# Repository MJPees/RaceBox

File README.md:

# RaceCollection Überblick

Die **RaceCollection** ist ein System für den Miniatur-Automobilsport, das verschiedene Komponenten zur präzisen Zeiterfassung und Rennsteuerung bietet.

---

### RFID-Connector

Der **RFID-Connector** fungiert als RFID-Empfänger. Er erfasst Fahrzeuge präzise und übermittelt die Zieldurchfahrten an Rennmanagement-Software wie **SmartRace** oder **CH-Racing-Club**.<br><br>
<a href="./RFID-Connector/README.md">Zum RFID-Connector</a><br><br>

-----

### GhostCar / Startampel-LED mit GhostCar

Diese Komponente bietet eine **GhostCar-Funktion**, bei der Sie gegen einen Carrera Hybrid Racer antreten können. Sie beinhaltet auch eine **Startampel-LED**. Ein zugehöriges Video zeigt das "GhostCar-StartingLights"-System in Aktion mit der "SmartRace"-Software. Es demonstriert den Countdown der Startampel, das "Go"-Signal mit grünen Lichtern, die GhostCar-Funktionalität, die Rundenzeiterfassung und die Rennsteuerung.<br><br>
<a href="./GhostCar/README.md">Zum GhostCar</a><br>
<br><br>

-----

### Startampel Display

Das **Startampel Display** ist eine separate Anzeigeeinheit für die Startampel.<br><br>
<a href="./StartingLightsDisplay/README.md">Zur Startampel</a><br>
<br><br><br>

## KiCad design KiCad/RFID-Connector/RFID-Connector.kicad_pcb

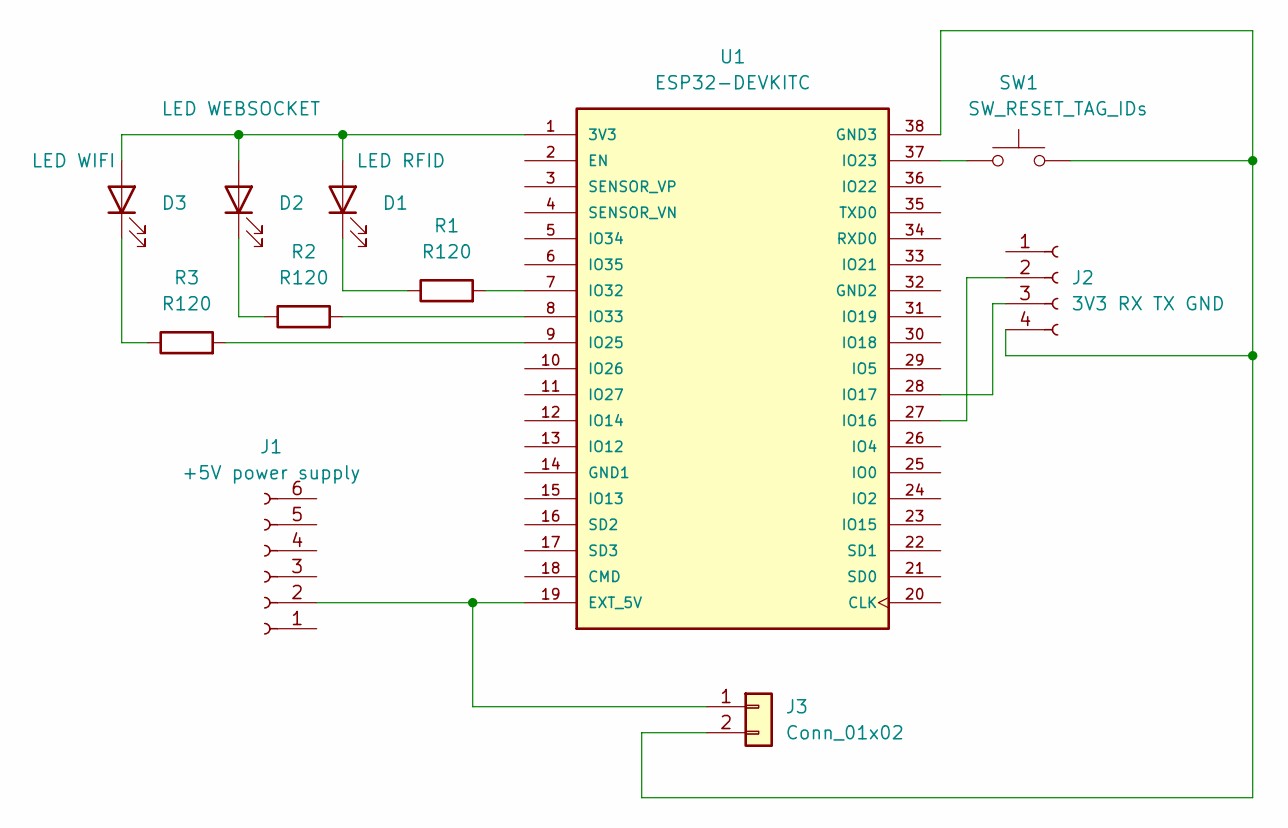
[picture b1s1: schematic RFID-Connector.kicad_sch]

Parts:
D1: LED RFID; LED_D3.0mm
D2: LED WEBSOCKET; LED_D3.0mm
D3: LED WIFI; LED_D3.0mm
J1: +5V power supply; PinHeader_1x06_P2.54mm_Vertical
J2: 3V3 RX TX GND; PinHeader_1x04_P2.54mm_Vertical
J3: Conn_01x02
R1, R2, R3: R120; R_Axial_DIN0204_L3.6mm_D1.6mm_P7.62mm_Horizontal
SW1: SW_RESET_TAG_IDs; SW_PUSH_6mm
U1: ESP32-DEVKITC; MODULE_ESP32-DEVKITC; PARTREV N/A

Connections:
unnamed: D1.1 (K), R1.1
unnamed: D1.2 (A), D2.2 (A), D3.2 (A), U1.1 (3V3)
unnamed: D2.1 (K), R2.1
unnamed: D3.1 (K), R3.1
unnamed: J1.2, J3.1, U1.19 (EXT_5V)
unnamed: J2.2, U1.27 (IO16)
unnamed: J2.3, U1.28 (IO17)
unnamed: J2.4, J3.2, SW1.2, U1.38 (GND3)
unnamed: R1.2, U1.7 (IO32)
unnamed: R2.2, U1.8 (IO33)
unnamed: R3.2, U1.9 (IO25)
unnamed: SW1.1, U1.37 (IO23)

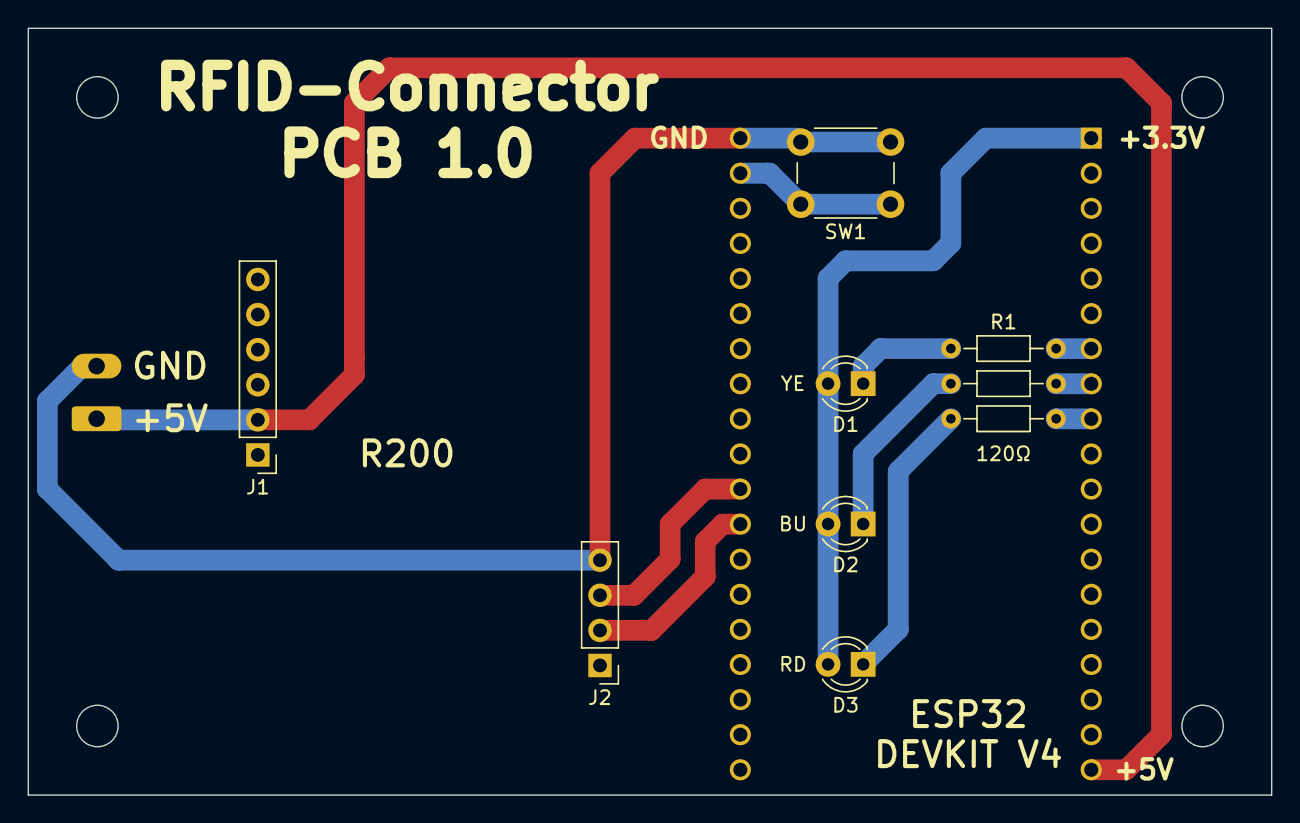
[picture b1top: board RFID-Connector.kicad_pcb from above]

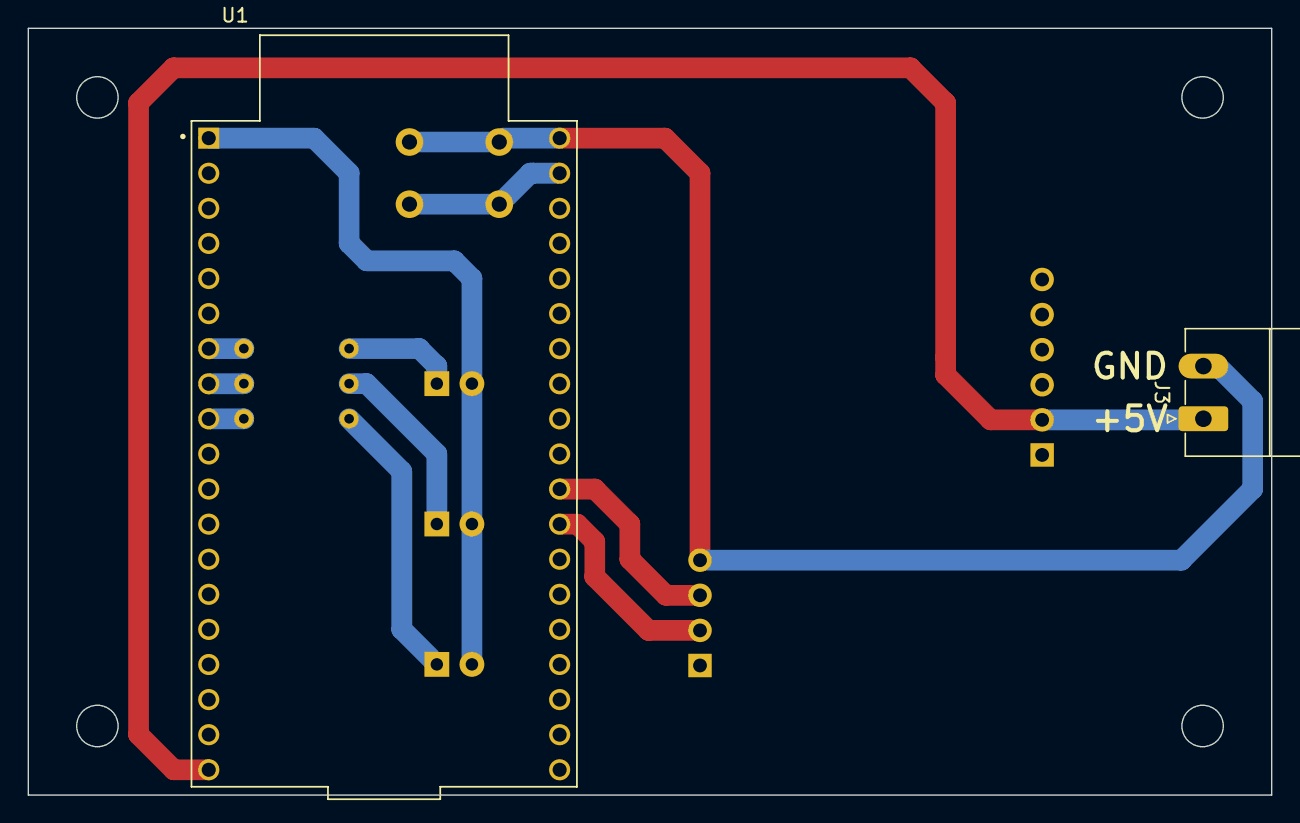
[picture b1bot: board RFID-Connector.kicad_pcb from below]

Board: 2 copper layers, 90.0 x 55.5 mm, 11 parts (2 on the bottom side), 12 nets.

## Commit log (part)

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2025-04-19 renamed ino file
2025-04-27 added Test
2025-04-27 deleted old files
2025-04-27 changes rfid read
2025-04-28 added wait time for startup rfid
2025-04-30 change power level from website
2025-04-30 removed r200 library
2025-05-01 fixed 11dbm value
2025-05-02 added images
2025-05-02 Erstentwurf Readme
2025-05-04 added min lap time to configuration (webpage)
2025-05-04 optimized min lap time
2025-05-04 fix optimized min lap time
2025-05-05 fixed 30 minutes timeout
2025-05-06 set power level without restart
2025-05-09 optimized communication
2025-05-09 changed bytes to unsigned char
2025-05-09 minor changes
2025-05-09 minor change
2025-05-09 8 cars possibel now. updated Readme
2025-05-09 updated images
2025-05-10 added Version information, Support for ESP32C3, added LapLed
2025-05-10 changed rx and tx pin at ESP32-C3 (wifi problems)
2025-05-10 bugfix wifi config
2025-05-10 bugfix dnsServer
2025-05-11 added setting led notification, fixed ap mode
2025-05-11 optimized startup
2025-05-11 added startup leds
2025-05-11 LAP LED bei ESP32-DEV auf D2 umgelegt, update Readme
2025-05-11 optimized r200 communication and wifi, bugfixes, LAP LED, ...
    - support for up to 8 cars
    - optimized r200 communication
    - fixed some wlan issues
    - added additional support for ESP32-C3
    - added optional LAP LED
2025-05-17 renamed led functions, added RFID label writer, updated Readme
2025-05-18 set wifi hostname to RFID-SmartRace
2025-05-20 hostname at webinterface, optimized performance of webinterface
2025-05-20 added CH-GhostCar-SmartRace
2025-05-20 CH-GhostCar-Smartrace - changed led pin
2025-05-21 feat: refactor default values, add CA to websocket client
2025-05-21 feat: optimize websocket reconnect
2025-05-21 feat: reduce magic numbers
2025-05-21 feat: make SSL CA certificate configurable via web interface
    - Added textarea field for ssl_ca_cert (PEM) in the configuration web page
    - ssl_ca_cert is now saved and loaded from preferences
    - Certificate is applied dynamically for websocket connections
    - Handles line breaks for compatibility with PEM format
2025-05-22 feat: replace unnecessary serverPort with apiKey in preferences
2025-05-22 feat(webui): add Alpine.js reactive select for targetSystem and conditional apiKey field
    - Integrated Alpine.js for reactive UI in the configuration web interface
    - Added select field for targetSystem with options "SmartRace" and "CH Racing Club"
    - ApiKey input is now only shown when "CH Racing Club" is selected
    - Preferences and config handling extended for targetSystem
2025-05-22 feat: adapt websocket payload format depending on selected target system
    - send_finish_line_message now builds the JSON payload differently for "ch_racing_club" and "smart_race"
    - For "ch_racing_club", sends command-based payload with api_key and rfid
    - For "smart_race", sends type-based payload with controller_id
    - Improves compatibility with multiple backend systems
2025-05-23 refactor: replace magic numbers for RFID counts with named constants
    - Introduced `RFID_MAX_COUNT` and `RFID_STORAGE_COUNT` to replace `max_rfid_cnt` and `storage_rfid_cnt`
    - Improved code clarity and maintainability by using named constants consistently
2025-05-23 refactor: extract WiFi reconnection logic into reloadWifi() helper
    - Moved repeated WiFi reconnection logic from `handleConfig()` to new `reloadWifi()` function
    - Improves code readability and reuse
2025-05-23 reduced magic numbers
2025-05-24 refactor: unify and extend configuration system with named fields
    - Replaced generic config variables with structured `config_*` names
    - Introduced `configuration_load()` and `configuration_save()` to encapsulate preferences handling
    - Added support for multiple target systems (`smart_race`, `ch_racing_club`)
    - Websocket and WiFi configuration now target-specific and modular
    - Renamed `reloadWifi()` to `wifi_reload()` for consistency
    - Improved serial output readability (prefixed log messages)
2025-05-24 refactor(checkRfid): simplify condition and avoid duplicate code
2025-05-25 feat: add JSON message formatting and deserialization with ArduinoJson
    - Use ArduinoJson to build and send websocket messages instead of manual string concatenation
    - Introduced lap time calculation for "ch_racing_club" payloads
    - Added JSON deserialization and error handling in `onMessageCallback()`
    - Improved log clarity with prefixed serial output
2025-05-25 fix: log prefix in onEventsCallback
2025-05-25 fix: websocket logging prefix
2025-05-25 chore: bump firmware version to 1.2.0
2025-05-25 fixed wifi reconnect , added simulator
2025-05-26 fixed webpage redirection
2025-05-26 fixed webpage redirect
2025-05-26 added websocket connected led
2025-05-27 disabled raising websocket backof for SmartRace, fixed websocket reconnect on wifi changes, optimized led functions
2025-05-31 fix: type of api key form input field
2025-05-31 feat: send target-specific connect message after websocket connection
    - Replaced hardcoded initial WebSocket messages with JSON payloads
    - Payload format now depends on `config_target_system`
    - `smart_race`: sends controller_set with controller_id "Z"
    - `ch_racing_club`: sends connect command with API key and device IP
2025-06-01 changed start multiRead
2025-06-01 fixed crash on wifi changes
2025-06-01 feat: send target-specific connect message after websocket connection (changed by endorfin)
2025-06-01 fix: possible crash on wifi changes, driving on config changes
2025-06-02 added hostname to serial output (only ble-mode)
2025-06-02 added hostname to serial output
2025-06-04 changed serial output, stop multiread at setReaderSetting()
2025-06-04 fixed stop multiRead on reboot of esp32
2025-06-04 ghostcar [ESP32-S3]: return to white led after braking (websocket connected led)
2025-06-04 fix: set lastEpcRead
2025-06-06 feat: dense-mode could be disabled for better rfid range
2025-06-07 ble + usb (2 Ghostcars) for ESP32S3
2025-06-07 renamed CH-GhostCar-SmartRace to RaceBox-GhostCar
2025-06-07 changed folder and ino-name of GhostCar
2025-06-07 renamed RFID-SmartRace to RaceBox. Added WIFI-AP-Mode led. LEDs can be inverted.
2025-06-07 corrected WIFI_AP_SSID
2025-06-07 raised default power level to 26, fixed default dense-mode
2025-06-08 added required libraries for ble
2025-06-08 feat: implement websocket commands fpr ch racing club
2025-06-08 fix: steering right stick
2025-06-09 fix: constant name for invert leds
2025-06-09 fix: constant name for invert leds (#9)
2025-06-09 fix: include for ESP32C3
2025-06-09 fix: wifi-ap-led not working
2025-06-09 added ble device name and version to connect message (ch_racing_club)
2025-06-09 added missing line break
2025-06-11 change dense mode by switch at runtime
2025-06-11 added windows flash scripts
2025-06-12 feat: switch sensitivity without reboot
2025-06-14 feat: update ch_racing_club websocket connect payload
2025-06-14 feat: add releases.json
2025-06-15 feat: added different starting lights, see config.h, renamed internal names to RaceBox-StartingLights
2025-06-16 feat: mini starting lights
2025-06-16 fix: support for 3 and 4 rows at 5 columns
2025-06-22 fix: suspended at SmartRace
2025-06-23 added dxf for cnc job
2025-06-23 fix: connect command / feat: optional potenimeter for speed
2025-06-24 feat: add RaceBox-StartingLightsDisplay to the project
2025-06-25 changed ch-racing-club update events
2025-06-25 moved libraries, work in progress
2025-06-25 updated releases.json
2025-06-25 fixed html headline
2025-06-26 debounced buttons
2025-06-26 Feat/optional led starting lights, optional start/stop buttons, optional potentimeter for ghostcar speed
    - added starting lights to ghostcar (optional)
    - added 2 buttons to start/stop (optional)
    - added potentimeter to change speed (optional)
2025-06-27 removed old flash-files, added files for github-workflow
2025-06-27 test for workflows
2025-06-27 missing .actrc for local instance of act
2025-06-27 fixed find boot_app0.bin
2025-06-27 installation of local libraries
2025-06-27 fixed import order
2025-06-27 hopeful last try...
2025-06-27 finally GhostCar-ESP32-C3
2025-06-27 fixes for github workflow
2025-06-27 fixes
2025-06-27 fixed script names
2025-06-27 added StartingLights
2025-06-27 removed date from zip-file
2025-06-27 added script-flash-files
2025-06-27 fix for ESP32C3
2025-06-28 Erste README für den flash-Vorgang
2025-06-29 Readme hinzugefügt.
2025-06-29 added flash instructions for windows, added startlinglightsdisplay flasher
2025-06-29 added RaceBox-StartingLightsDisplay and added windows instructions
2025-06-29 added hint download raw file
2025-06-29 fixed bootloader startaddress for ESP32S3 and ESP32C3
2025-06-29 fixed bootloader address
2025-06-29 added hint for flash-mode (ESP32C3/S3)
2025-06-29 updated flasher files
2025-06-29 build on flash-script changes
2025-06-30 added RaceBox-GhostCar-StartingLights-ESP32S3-Poti video to README.md
2025-06-30 fixed demo video (github does not support iframes)
2025-06-30 added images of RaceBox-StartingLightsDisplay to README
2025-06-30 resized images
2025-06-30 updated version
2025-06-30 updated flasher to last version
2025-07-02 changed pin of switch
2025-07-03 prepared for RaceBox_PCB_V1.0
2025-07-03 added build script for RaceBox-PCB_V1.0
2025-07-03 added logging changes to ino-file
2025-07-04 added status leds for ESP32-C3, prepared for pace car button
2025-07-04 added PACECAR_BUTTON_PIN to ESP32-S3
2025-07-04 fixed missing declaration
2025-07-06 updated versions
2025-07-06 updated script-flasher files
2025-07-09 prepared to remove label RaceBox, changed back to wifi-ap-mode led, added directory sdcard to StartingLightsDisplay flasher, added BLE name to webconfig.
2025-07-09 fixed adding sdcard
2025-07-09 changed RaceBox to RFID-Connector
2025-07-09 fixed rfid-connector pcb
2025-07-09 added flasher zip files
2025-07-09 work in progress - README
2025-07-11 update artifact directory structure and adjust WiFi connection parameters in firmware
2025-07-11 updated PCB
2025-07-11 update version to 1.0.2, adjust WiFi connection parameters, and implement red flag functionality
2025-07-11 Add README documentation and images for RFID-Connector
2025-07-11 Fix filename typos in ESP32 flash script for linux
2025-07-11 fixed pushbutton function
2025-07-11 added led test at startup for 1 second
2025-07-12 fixed pcb
2025-07-12 added solder helper for pcb
2025-07-14 added power connector to pcb
2025-07-20 refactor: update variable names for consistency and clarity; added controllerId for SmartRace to webconfig; bump version to 1.4.0
2025-07-20 updated GhostCar flash files
2025-07-21 refactor: rename configuration functions for consistency; optimized wifi connect
2025-07-22 refactor: update variable names for consistency and clarity; added label writer (not tested); optimized wifi connect;
2025-07-22 test if stop read is needed for restart multiread. (speedup)
2025-07-22 optimized loop for rfid-reading performance.
2025-07-22 fixed/tested label writer;
2025-07-23 fixed rfidRead()
2025-07-23 fixed reboot on websocket connect failure
2025-07-23 updated RFID-Connector flasher; ready for testing;
2025-07-27 updated EPC label in webconfig; rfid LED flashes only on message send
2025-07-27 fixed read time delay issue on multiple tags
